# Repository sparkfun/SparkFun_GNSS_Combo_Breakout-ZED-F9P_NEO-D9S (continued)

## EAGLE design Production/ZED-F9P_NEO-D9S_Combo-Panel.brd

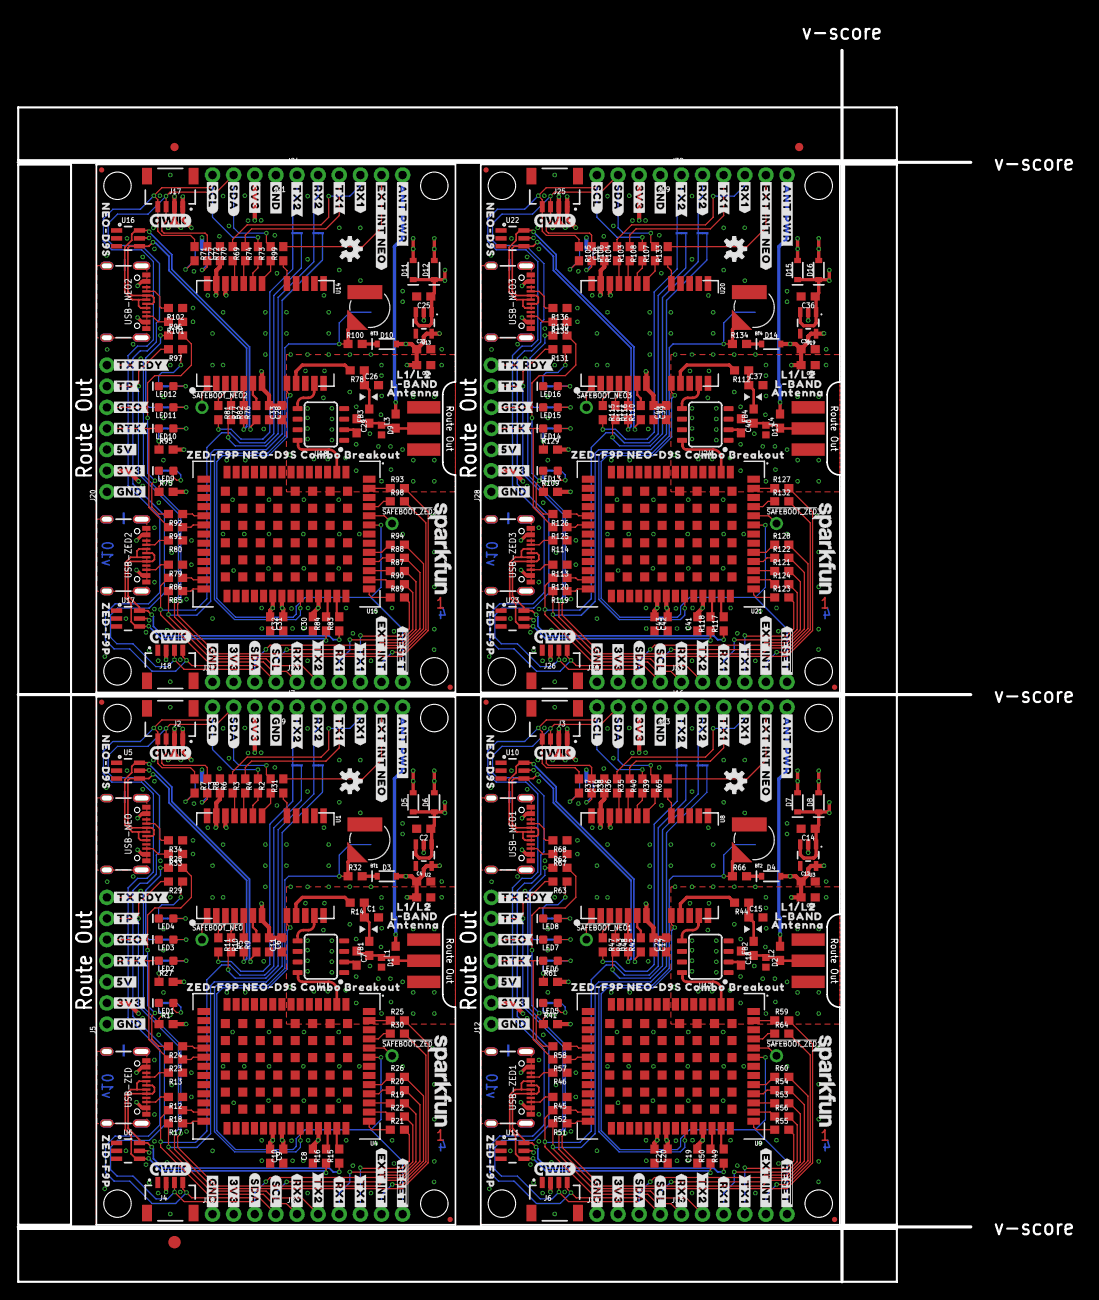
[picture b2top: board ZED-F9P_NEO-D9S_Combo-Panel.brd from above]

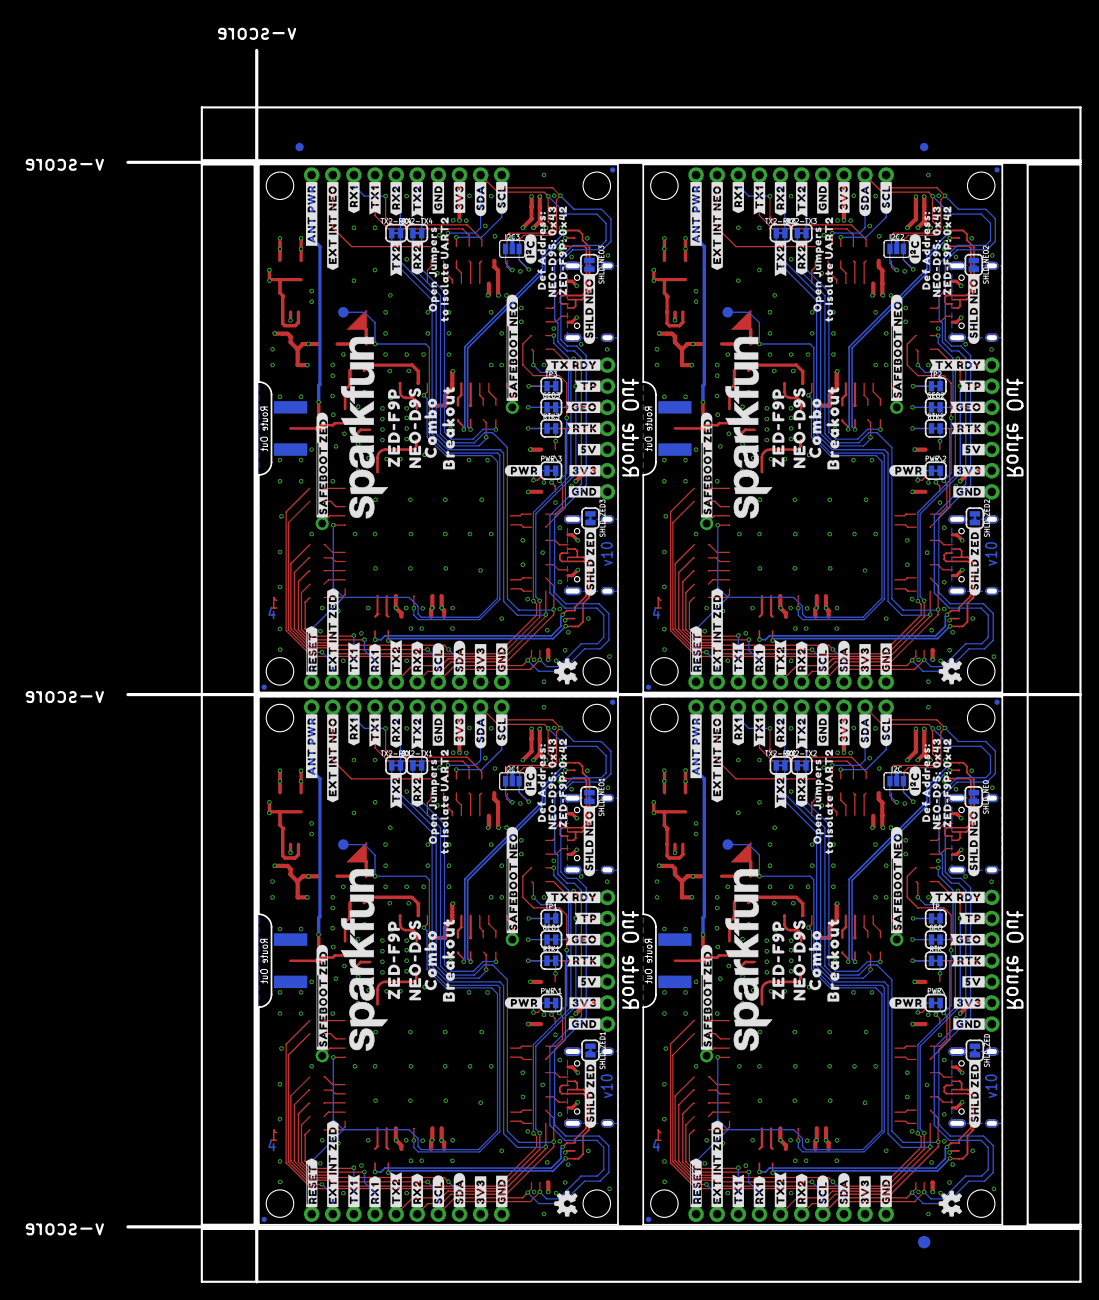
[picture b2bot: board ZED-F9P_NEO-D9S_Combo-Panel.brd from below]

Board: 4 copper layers, 114.6 x 148.1 mm, 714 parts (243 on the bottom side), 300 nets.

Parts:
!SAFEBOOT_NEO!, !SAFEBOOT_NEO!1, !SAFEBOOT_NEO!2, !SAFEBOOT_NEO!3: TEST-POINTPOGO_PTH; 1X01_NO_SILK
!SAFEBOOT_ZED!, !SAFEBOOT_ZED!1, !SAFEBOOT_ZED!2, !SAFEBOOT_ZED!3: TEST-POINTPOGO_PTH; 1X01_NO_SILK
BT1, BT2, BT3, BT4: RELOWABLE_BATTERY_MS421R; MS421R_IV03E
C1, C7, C15, C18, C26, C29, C37, C40: 47pF; 0603
C2, C3, C4, C6, C8, C9, C12, C14, C16, C17, C19, C20, C23, C25, C27, C28, C30, C31, C34, C36, C38, C39, C41, C42: 1.0uF; 0603
C5, C10, C11, C13, C21, C22, C24, C32, C33, C35, C43, C44: 0.1uF; 0603
D1, D2, D9, D13: PESD0402-0402; 0402
D3, D4, D10, D14: 0.5A/40V/420mV; SOD-323
D5, D6, D7, D8, D11, D12, D15, D16: 1A/23V/620mV; SOD-323
E$1, E$2, E$3, E$4: FIDUCIAL-1X2
E$5, E$6: FIDUCIAL-1.5X3
FB1, FB2, FB3, FB4: 30Ω/1.8A; 0603
GEO, GEO1, GEO2, GEO3: JUMPER-SMT_2_NC_TRACE_SILK; SMT-JUMPER_2_NC_TRACE_SILK
I2C, I2C1, I2C2, I2C3: JUMPER-SMT_3_NO_SILK; SMT-JUMPER_3_NO_SILK
J1, J11, J19, J27: ANTENNA-SMA-GROUNDEDEDGE_SMA; SMA-EDGE
J2, J3, J4, J6, J17, J18, J25, J26: Qwiic Right Angle; JST04_1MM_RA
J5, J12, J20, J28: 1X07_NO_SILK
J7, J8, J15, J16, J23, J24, J31, J32: 1X06_NO_SILK
J9, J10, J13, J14, J21, J22, J29, J30: 1X04_NO_SILK
JP1, JP2, JP7, JP8, JP9, JP10, JP15, JP16, JP17, JP18, JP24, JP25, JP31, JP41, JP91, JP101: STAND-OFF
JP3, JP4, JP5, JP6, JP11, JP12, JP13, JP14, JP19, JP20, JP21, JP22, JP23, JP61, JP71, JP81: FIDUCIALUFIDUCIAL; MICRO-FIDUCIAL
L1, L2, L3, L4: DNP; 0603_NO-CREAM
LED1, LED5, LED9, LED13: RED; LED-0603
LED2, LED3, LED4, LED6, LED7, LED8, LED10, LED11, LED12, LED14, LED15, LED16: BLUE; LED-0603
LOGO1, LOGO4, LOGO5, LOGO7, LOGO11, LOGO12, LOGO16, LOGO17: OSHW-LOGOS; OSHW-LOGO-S
LOGO2, LOGO8, LOGO13, LOGO18: SFE_LOGO_NAME.1_INCH; SFE_LOGO_NAME_.1
LOGO3, LOGO6, LOGO9, LOGO10, LOGO14, LOGO15, LOGO19, LOGO20: QWIIC_LOGO_5MM; QWIIC_5MM
PWR\, PWR\1, PWR\2, PWR\3: JUMPER-SMT_2_NC_TRACE_SILK; SMT-JUMPER_2_NC_TRACE_SILK
R1, R41, R75, R109: 4.7k; 0603
R2, R3, R4, R5, R6, R11, R17, R18, R19, R20, R21, R22, R23, R24, R25, R26, R30, R31, R35, R36, R39, R40, R47, R48, R51, R52, R53, R54, R55, R56, R57, R58, R59, R60, R64, R65, R69, R70, R73, R74, R81, R82, R85, R86, R87, R88, R89, R90, R91, R92, R93, R94, R98, R99, R103, R104, R107, R108, R115, R116, R119, R120, R121, R122, R123, R124, R125, R126, R127, R128, R132, R133: 33; 0603
R7, R8, R37, R38, R71, R72, R105, R106: 2.2k; 0603
R9, R10, R15, R16, R42, R43, R49, R50, R76, R77, R83, R84, R110, R111, R117, R118: 27; 0603
R12, R13, R33, R34, R45, R46, R67, R68, R79, R80, R101, R102, R113, R114, R135, R136: 5.1k; 0603
R14, R44, R78, R112: 10; 0603
R27, R28, R29, R61, R62, R63, R95, R96, R97, R129, R130, R131: 1k; 0603
R32, R66, R100, R134: 3.3k; 0603
RTK, RTK1, RTK2, RTK3: JUMPER-SMT_2_NC_TRACE_SILK; SMT-JUMPER_2_NC_TRACE_SILK
RX2-TX1, RX2-TX2, RX2-TX3, RX2-TX4: JUMPER-SMT_2_NC_TRACE_SILK; SMT-JUMPER_2_NC_TRACE_SILK
SHLD_NEO, SHLD_NEO1, SHLD_NEO2, SHLD_NEO3: JUMPER-SMT_2_NC_TRACE_SILK; SMT-JUMPER_2_NC_TRACE_SILK
SHLD_ZED, SHLD_ZED1, SHLD_ZED2, SHLD_ZED3: JUMPER-SMT_2_NC_TRACE_SILK; SMT-JUMPER_2_NC_TRACE_SILK
TP, TP1, TP2, TP3: JUMPER-SMT_2_NC_TRACE_SILK; SMT-JUMPER_2_NC_TRACE_SILK
TX2-RX1, TX2-RX2, TX2-RX3, TX2-RX4: JUMPER-SMT_2_NC_TRACE_SILK; SMT-JUMPER_2_NC_TRACE_SILK
U1, U8, U14, U20: U-BLOX_NEO-D9S-00B; NEO-M9N/M8T/M8U/D9S
U2, U3, U13, U19: 3.3V; SOT23-5
U4, U9, U15, U21: U-BLOX_ZED-F9P; ZED-F9P
U5, U6, U10, U11, U16, U17, U22, U23: ESD Diode; SOT-23-6
U7, U12, U18, U24: BP2G1+_POWER_SPLITTER; XX21
U$1, U$2, U$3, U$38, U$77, U$83, U$161, U$162, U$163, U$241, U$242, U$243: #GND#0
U$4, U$5, U$6, U$84, U$85, U$86, U$164, U$165, U$166, U$244, U$245, U$246: #GND#1
U$7, U$144, U$224, U$304: #SHLD_ZED#15
U$8, U$10, U$126, U$127, U$206, U$207, U$286, U$287: #SDA#0
U$9, U$13, U$130, U$131, U$210, U$211, U$290, U$291: #SCL#0
U$11, U$12, U$128, U$129, U$208, U$209, U$288, U$289: #SDA#1
U$14, U$153, U$233, U$313: L#BAND18
U$15, U$30, U$132, U$133, U$212, U$213, U$292, U$293: #SCL#1
U$16, U$100, U$180, U$260: #RTK#0
U$17, U$101, U$181, U$261: #RTK#1
U$18, U$102, U$182, U$262: #GEO#0
U$19, U$103, U$183, U$263: #GEO#1
U$20, U$87, U$167, U$247: #5V#0
U$21, U$88, U$168, U$248: #5V#6
U$22, U$23, U$56, U$89, U$90, U$97, U$169, U$170, U$177, U$249, U$250, U$257: #3V3#0
U$24, U$25, U$70, U$91, U$92, U$139, U$171, U$172, U$219, U$251, U$252, U$299: #3V3#4
U$26, U$104, U$184, U$264: #TP#0
U$27, U$105, U$185, U$265: #TP#1
U$28, U$106, U$186, U$266: #TX_RDY#0
U$29, U$107, U$187, U$267: #TX_RDY#1
U$31, U$39, U$40, U$112, U$113, U$134, U$192, U$193, U$214, U$272, U$273, U$294: #TX2#0
U$32, U$34, U$35, U$108, U$109, U$135, U$188, U$189, U$215, U$268, U$269, U$295: #RX2#0
U$33, U$151, U$231, U$311: L1#L218
U$36, U$37, U$110, U$111, U$190, U$191, U$270, U$271: #RX2#3
U$41, U$42, U$114, U$115, U$194, U$195, U$274, U$275: #TX2#3
U$43, U$44, U$116, U$117, U$196, U$197, U$276, U$277: #RX1#0
U$45, U$93, U$173, U$253: ##RESET##0
U$46, U$94, U$174, U$254: ##RESET##1
U$47, U$95, U$175, U$255: #EXT_INT#0
U$48, U$140, U$220, U$300: #EXT_INT_ZED#0
U$49, U$50, U$118, U$119, U$198, U$199, U$278, U$279: #RX1#2
U$51, U$57, U$120, U$121, U$200, U$201, U$280, U$281: #TX1#0
U$52, U$96, U$176, U$256: #I�C#0
U$53, U$145, U$225, U$305: #SHLD_NEO#12
U$54, U$152, U$232, U$312: ANTENNA18
U$55, U$147, U$227, U$307: NEO#D9S16
U$58, U$98, U$178, U$258: #ANT_PWR#0
U$59, U$99, U$179, U$259: #ANT_PWR#1
U$60, U$61, U$122, U$123, U$202, U$203, U$282, U$283: #TX1#2
U$62, U$124, U$204, U$284: #EXT_INT_NEO#0
U$63, U$125, U$205, U$285: #EXT_INT_NEO#1
U$64, U$148, U$228, U$308: COMBO16
U$65, U$136, U$216, U$296: ZED#F9P10
U$66, U$137, U$217, U$297: NEO#D9S10
U$67, U$149, U$229, U$309: BREAKOUT17
U$68, U$150, U$230, U$310: SFE_LOGO_NAME_.2
U$69, U$138, U$218, U$298: #PWR#0
U$71, U$142, U$222, U$302: ##SAFEBOOT#_NEO#13
U$72, U$143, U$223, U$303: ##SAFEBOOT#_ZED#14
U$73, U$154, U$234, U$314: OPEN_JUMPERS13
U$74, U$155, U$235, U$315: TO_ISOLATE_UART214
U$75, U$141, U$221, U$301: ZED#F9P_NEO#D9S_COMBO_BREAKOUT0
U$76, U$156, U$236, U$316: DEF_ADDRESS#_12
U$78, U$146, U$226, U$306: ZED#F9P16
U$79, U$157, U$237, U$317: NEO#D9S#13
U$80, U$158, U$238, U$318: ZED#F9P#13
U$81, U$159, U$239, U$319: 0X4313
U$82, U$160, U$240, U$320: 0X4213
USB-NEO, USB-NEO1, USB-NEO2, USB-NEO3: USB Female Type C Connector; USB-C-16P_4LAYER-PADS
USB-ZED, USB-ZED1, USB-ZED2, USB-ZED3: USB Female Type C Connector; USB-C-16P_4LAYER-PADS
V_BKCP, V_BKCP1, V_BKCP2, V_BKCP3: TEST-POINT3X5; PAD.03X.05

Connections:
3.3V: C3.1, C4.1, C5.2, C6.1, C8.2, C9.1, C10.2, C11.2, D3.A, I2C.2, J2.2, J4.2, J5.2, J9.2, J10.2, R1.2, R27.2, U1.7, U1.22, U1.23, U2.5, U4.33, U4.34, U4.38
3.3V1: C12.1, C13.2, C16.1, C17.1, C19.2, C20.1, C21.2, C22.2, D4.A, I2C1.2, J3.2, J6.2, J12.2, J13.2, J14.2, R41.2, R61.2, U3.5, U8.7, U8.22, U8.23, U9.33, U9.34, U9.38
3.3V2: C23.1, C24.2, C27.1, C28.1, C30.2, C31.1, C32.2, C33.2, D10.A, I2C2.2, J17.2, J18.2, J20.2, J21.2, J22.2, R75.2, R95.2, U13.5, U14.7, U14.22, U14.23, U15.33, U15.34, U15.38
3.3V3: C34.1, C35.2, C38.1, C39.1, C41.2, C42.1, C43.2, C44.2, D14.A, I2C3.2, J25.2, J26.2, J28.2, J29.2, J30.2, R109.2, R129.2, U19.5, U20.7, U20.22, U20.23, U21.33, U21.34, U21.38
5V: C2.1, D5.C, D6.C, J5.3, U2.1, U2.3
5V1: C14.1, D7.C, D8.C, J12.3, U3.1, U3.3
5V2: C25.1, D11.C, D12.C, J20.3, U13.1, U13.3
5V3: C36.1, D15.C, D16.C, J28.3, U19.1, U19.3
!RESET!: J8.6, U1.8, U4.49
!RESET!1: J15.6, U8.8, U9.49
!RESET!2: J23.6, U14.8, U15.49
!RESET!3: J31.6, U20.8, U21.49
!SAFEBOOT_NEO!: !SAFEBOOT_NEO!.1, U1.1
!SAFEBOOT_NEO!1: !SAFEBOOT_NEO!1.1, U8.1
!SAFEBOOT_NEO!2: !SAFEBOOT_NEO!2.1, U14.1
!SAFEBOOT_NEO!3: !SAFEBOOT_NEO!3.1, U20.1
!SAFEBOOT_ZED!: !SAFEBOOT_ZED!.1, U4.50
!SAFEBOOT_ZED!1: !SAFEBOOT_ZED!1.1, U9.50
!SAFEBOOT_ZED!2: !SAFEBOOT_ZED!2.1, U15.50
!SAFEBOOT_ZED!3: !SAFEBOOT_ZED!3.1, U21.50
ANT: C7.2, U7.2
ANT1: C18.2, U12.2
ANT2: C29.2, U18.2
ANT3: C40.2, U24.2
ANT_NEO: U1.11, U7.5
ANT_NEO1: U8.11, U12.5
ANT_NEO2: U14.11, U18.5
ANT_NEO3: U20.11, U24.5
ANT_PWR: J7.6, L1.2
ANT_PWR1: J16.6, L2.2
ANT_PWR2: J24.6, L3.2
ANT_PWR3: J32.6, L4.2
ANT_VCC: C1.1, FB1.2, R14.1
ANT_VCC1: C15.1, FB2.2, R44.1
ANT_VCC2: C26.1, FB3.2, R78.1
ANT_VCC3: C37.1, FB4.2, R112.1
ANT_ZED: U4.2, U7.8
ANT_ZED1: U9.2, U12.8
ANT_ZED2: U15.2, U18.8
ANT_ZED3: U21.2, U24.8
D+_NEO: R9.1, U5.6, USB-NEO.A6, USB-NEO.B6
D+_NEO1: R42.1, U10.6, USB-NEO1.A6, USB-NEO1.B6
D+_NEO2: R76.1, U16.6, USB-NEO2.A6, USB-NEO2.B6
D+_NEO3: R110.1, U22.6, USB-NEO3.A6, USB-NEO3.B6
D+_ZED: R15.1, U6.6, USB-ZED.A6, USB-ZED.B6
D+_ZED1: R49.1, U11.6, USB-ZED1.A6, USB-ZED1.B6
D+_ZED2: R83.1, U17.6, USB-ZED2.A6, USB-ZED2.B6
D+_ZED3: R117.1, U23.6, USB-ZED3.A6, USB-ZED3.B6
D-_NEO: R10.1, U5.4, USB-NEO.A7, USB-NEO.B7
D-_NEO1: R43.1, U10.4, USB-NEO1.A7, USB-NEO1.B7
D-_NEO2: R77.1, U16.4, USB-NEO2.A7, USB-NEO2.B7
D-_NEO3: R111.1, U22.4, USB-NEO3.A7, USB-NEO3.B7
D-_ZED: R16.1, U6.4, USB-ZED.A7, USB-ZED.B7
D-_ZED1: R50.1, U11.4, USB-ZED1.A7, USB-ZED1.B7
D-_ZED2: R84.1, U17.4, USB-ZED2.A7, USB-ZED2.B7
D-_ZED3: R118.1, U23.4, USB-ZED3.A7, USB-ZED3.B7
EXT_INT_NEO: J7.5, R31.2
EXT_INT_NEO1: J16.5, R65.2
EXT_INT_NEO2: J24.5, R99.2
EXT_INT_NEO3: J32.5, R133.2
EXT_INT_ZED: J8.5, R30.2
EXT_INT_ZED1: J15.5, R64.2
EXT_INT_ZED2: J23.5, R98.2
EXT_INT_ZED3: J31.5, R132.2
GEO: J5.5, R24.2, R28.2
GEO1: J12.5, R58.2, R62.2
GEO2: J20.5, R92.2, R96.2
GEO3: J28.5, R126.2, R130.2
GND: BT1.-, C1.2, C2.2, C3.2, C4.2, C5.1, C6.2, C8.1, C9.2, C10.1, C11.1, D1.2, J1.GND@0, J1.GND@1, J1.GND@2, J1.GND@3, J2.1, J4.1, J5.1, J9.1, J10.1, LED1.C, LED3.C, LED4.C, R12.1, R13.1, R33.1, R34.1, SHLD_NEO.1, SHLD_ZED.1, U1.10, U1.12, U1.13, U1.24, U2.2, U4.1, U4.3, U4.12, U4.14, U4.32, U4.37, U4.41, U4.48, U4.55, U4.56, U4.57, U4.58, U4.59, U4.60, U4.61, U4.62, U4.63, U4.64, U4.65, U4.66, U4.67, U4.68, U4.69, U4.70, U4.71, U4.72, U4.73, U4.74, U4.75, U4.76, U4.77, U4.78, U4.79, U4.80, U4.81, U4.82, U4.83, U4.84, U4.85, U4.86, U4.87, U4.88, U4.89, U4.90, U4.91, U4.92, U4.93, U4.94, U4.95, U4.96, U4.97, U4.98, U4.99, U4.100, U4.101, U4.102, U5.2, U6.2, U7.1, U7.3, U7.4, U7.6, U7.7, USB-NEO.GND, USB-NEO.GND2, USB-ZED.GND, USB-ZED.GND2
GND1: BT2.-, C12.2, C13.1, C14.2, C15.2, C16.2, C17.2, C19.1, C20.2, C21.1, C22.1, D2.2, J3.1, J6.1, J11.GND@0, J11.GND@1, J11.GND@2, J11.GND@3, J12.1, J13.1, J14.1, LED5.C, LED7.C, LED8.C, R45.1, R46.1, R67.1, R68.1, SHLD_NEO1.1, SHLD_ZED1.1, U3.2, U8.10, U8.12, U8.13, U8.24, U9.1, U9.3, U9.12, U9.14, U9.32, U9.37, U9.41, U9.48, U9.55, U9.56, U9.57, U9.58, U9.59, U9.60, U9.61, U9.62, U9.63, U9.64, U9.65, U9.66, U9.67, U9.68, U9.69, U9.70, U9.71, U9.72, U9.73, U9.74, U9.75, U9.76, U9.77, U9.78, U9.79, U9.80, U9.81, U9.82, U9.83, U9.84, U9.85, U9.86, U9.87, U9.88, U9.89, U9.90, U9.91, U9.92, U9.93, U9.94, U9.95, U9.96, U9.97, U9.98, U9.99, U9.100, U9.101, U9.102, U10.2, U11.2, U12.1, U12.3, U12.4, U12.6, U12.7, USB-NEO1.GND, USB-NEO1.GND2, USB-ZED1.GND, USB-ZED1.GND2
GND2: BT3.-, C23.2, C24.1, C25.2, C26.2, C27.2, C28.2, C30.1, C31.2, C32.1, C33.1, D9.2, J17.1, J18.1, J19.GND@0, J19.GND@1, J19.GND@2, J19.GND@3, J20.1, J21.1, J22.1, LED9.C, LED11.C, LED12.C, R79.1, R80.1, R101.1, R102.1, SHLD_NEO2.1, SHLD_ZED2.1, U13.2, U14.10, U14.12, U14.13, U14.24, U15.1, U15.3, U15.12, U15.14, U15.32, U15.37, U15.41, U15.48, U15.55, U15.56, U15.57, U15.58, U15.59, U15.60, U15.61, U15.62, U15.63, U15.64, U15.65, U15.66, U15.67, U15.68, U15.69, U15.70, U15.71, U15.72, U15.73, U15.74, U15.75, U15.76, U15.77, U15.78, U15.79, U15.80, U15.81, U15.82, U15.83, U15.84, U15.85, U15.86, U15.87, U15.88, U15.89, U15.90, U15.91, U15.92, U15.93, U15.94, U15.95, U15.96, U15.97, U15.98, U15.99, U15.100, U15.101, U15.102, U16.2, U17.2, U18.1, U18.3, U18.4, U18.6, U18.7, USB-NEO2.GND, USB-NEO2.GND2, USB-ZED2.GND, USB-ZED2.GND2
GND3: BT4.-, C34.2, C35.1, C36.2, C37.2, C38.2, C39.2, C41.1, C42.2, C43.1, C44.1, D13.2, J25.1, J26.1, J27.GND@0, J27.GND@1, J27.GND@2, J27.GND@3, J28.1, J29.1, J30.1, LED13.C, LED15.C, LED16.C, R113.1, R114.1, R135.1, R136.1, SHLD_NEO3.1, SHLD_ZED3.1, U19.2, U20.10, U20.12, U20.13, U20.24, U21.1, U21.3, U21.12, U21.14, U21.32, U21.37, U21.41, U21.48, U21.55, U21.56, U21.57, U21.58, U21.59, U21.60, U21.61, U21.62, U21.63, U21.64, U21.65, U21.66, U21.67, U21.68, U21.69, U21.70, U21.71, U21.72, U21.73, U21.74, U21.75, U21.76, U21.77, U21.78, U21.79, U21.80, U21.81, U21.82, U21.83, U21.84, U21.85, U21.86, U21.87, U21.88, U21.89, U21.90, U21.91, U21.92, U21.93, U21.94, U21.95, U21.96, U21.97, U21.98, U21.99, U21.100, U21.101, U21.102, U22.2, U23.2, U24.1, U24.3, U24.4, U24.6, U24.7, USB-NEO3.GND, USB-NEO3.GND2, USB-ZED3.GND, USB-ZED3.GND2
unnamed: PWR\.2, R1.1
unnamed: R3.1, U1.20
unnamed: R2.1, U1.18
unnamed: R4.1, U1.19
unnamed: I2C.1, R8.2
unnamed: R6.1, U1.21
unnamed: R12.2, USB-ZED.B5
unnamed: I2C.3, R7.2
unnamed: R13.2, USB-ZED.A5
unnamed: LED1.A, PWR\.1
unnamed: R9.2, U1.6
unnamed: R10.2, U1.5
unnamed: D3.C, R32.2
unnamed: R11.1, U1.3
unnamed: R5.1, U1.4
unnamed: R15.2, U4.40
unnamed: R16.2, U4.39
unnamed: R19.1, U4.44
unnamed: R20.1, U4.45
unnamed: R21.1, U4.42
unnamed: R22.1, U4.43
unnamed: R26.1, U4.46
unnamed: LED2.A, RTK.1
unnamed: R17.1, U4.27
unnamed: R18.1, U4.26
unnamed: GEO.1, LED3.A
unnamed: LED4.A, TP.1
unnamed: R27.1, RTK.2
unnamed: GEO.2, R28.1
unnamed: R29.1, TP.2
unnamed: R30.1, U4.51
unnamed: R31.1, U1.17
unnamed: R33.2, USB-NEO.B5
unnamed: R34.2, USB-NEO.A5
unnamed: R23.1, U4.20
unnamed: R24.1, U4.19
unnamed: R25.1, U4.53
unnamed: I2C1.1, R38.2
unnamed: I2C1.3, R37.2
unnamed: R42.2, U8.6
unnamed: R43.2, U8.5
unnamed: R45.2, USB-ZED1.B5
unnamed: R46.2, USB-ZED1.A5
unnamed: R47.1, U8.3
unnamed: R48.1, U8.4
unnamed: R35.1, U8.20
unnamed: R36.1, U8.21
unnamed: R39.1, U8.18
unnamed: R40.1, U8.19
unnamed: R49.2, U9.40
unnamed: R50.2, U9.39
unnamed: R53.1, U9.44
unnamed: R54.1, U9.45
unnamed: R55.1, U9.42
unnamed: R56.1, U9.43
unnamed: R51.1, U9.27
unnamed: R52.1, U9.26
unnamed: R60.1, U9.46
unnamed: LED6.A, RTK1.1
unnamed: GEO1.1, LED7.A
unnamed: LED8.A, TP1.1
unnamed: R61.1, RTK1.2
unnamed: GEO1.2, R62.1
unnamed: R63.1, TP1.2
unnamed: R57.1, U9.20
unnamed: R58.1, U9.19
unnamed: R59.1, U9.53
unnamed: R64.1, U9.51
unnamed: R65.1, U8.17
unnamed: D4.C, R66.2
unnamed: R67.2, USB-NEO1.B5
unnamed: R68.2, USB-NEO1.A5
unnamed: PWR\1.2, R41.1
unnamed: LED5.A, PWR\1.1
unnamed: I2C2.1, R72.2
unnamed: I2C2.3, R71.2
unnamed: R76.2, U14.6
unnamed: R77.2, U14.5
unnamed: R79.2, USB-ZED2.B5
unnamed: R80.2, USB-ZED2.A5
unnamed: R81.1, U14.3
unnamed: R82.1, U14.4
unnamed: R69.1, U14.20
unnamed: R70.1, U14.21
unnamed: R73.1, U14.18
unnamed: R74.1, U14.19
unnamed: R83.2, U15.40
unnamed: R84.2, U15.39
unnamed: R87.1, U15.44
unnamed: R88.1, U15.45
unnamed: R89.1, U15.42
unnamed: R90.1, U15.43
unnamed: R85.1, U15.27
unnamed: R86.1, U15.26
unnamed: R94.1, U15.46
unnamed: LED10.A, RTK2.1
unnamed: GEO2.1, LED11.A
unnamed: LED12.A, TP2.1
unnamed: R95.1, RTK2.2
unnamed: GEO2.2, R96.1
unnamed: R97.1, TP2.2
unnamed: R91.1, U15.20
unnamed: R92.1, U15.19
unnamed: R93.1, U15.53
unnamed: R98.1, U15.51
unnamed: R99.1, U14.17
unnamed: D10.C, R100.2
unnamed: R101.2, USB-NEO2.B5
unnamed: R102.2, USB-NEO2.A5
unnamed: PWR\2.2, R75.1
unnamed: LED9.A, PWR\2.1
unnamed: I2C3.1, R106.2
unnamed: I2C3.3, R105.2
unnamed: R110.2, U20.6
unnamed: R111.2, U20.5
unnamed: R113.2, USB-ZED3.B5
unnamed: R114.2, USB-ZED3.A5
unnamed: R115.1, U20.3
unnamed: R116.1, U20.4
unnamed: R103.1, U20.20
unnamed: R104.1, U20.21
unnamed: R107.1, U20.18
unnamed: R108.1, U20.19
unnamed: R117.2, U21.40
unnamed: R118.2, U21.39
unnamed: R121.1, U21.44
unnamed: R122.1, U21.45
unnamed: R123.1, U21.42
unnamed: R124.1, U21.43
unnamed: R119.1, U21.27
unnamed: R120.1, U21.26
unnamed: R128.1, U21.46
unnamed: LED14.A, RTK3.1
unnamed: GEO3.1, LED15.A
unnamed: LED16.A, TP3.1
unnamed: R129.1, RTK3.2
unnamed: GEO3.2, R130.1
unnamed: R131.1, TP3.2
unnamed: R125.1, U21.20
unnamed: R126.1, U21.19
unnamed: R127.1, U21.53
unnamed: R132.1, U21.51
unnamed: R133.1, U20.17
unnamed: D14.C, R134.2
unnamed: R135.2, USB-NEO3.B5
unnamed: R136.2, USB-NEO3.A5
unnamed: PWR\3.2, R109.1
unnamed: LED13.A, PWR\3.1
RTK: J5.4, LED2.C, R23.2
RTK1: J12.4, LED6.C, R57.2
RTK2: J20.4, LED10.C, R91.2
RTK3: J28.4, LED14.C, R125.2
RXD1_NEO: J7.4, R6.2
RXD1_NEO1: J16.4, R36.2
RXD1_NEO2: J24.4, R70.2
RXD1_NEO3: J32.4, R104.2
RXD1_ZED: J8.3, R22.2
RXD1_ZED1: J15.3, R56.2
RXD1_ZED2: J23.3, R90.2
RXD1_ZED3: J31.3, R124.2
RXD2_NEO: J7.2, R5.2, TX2-RX2.2
RXD2_NEO1: J16.2, R48.2, TX2-RX1.2
RXD2_NEO2: J24.2, R82.2, TX2-RX3.2
RXD2_NEO3: J32.2, R116.2, TX2-RX4.2
RXD2_ZED: J8.1, R18.2, RX2-TX2.1
RXD2_ZED1: J15.1, R52.2, RX2-TX1.1
RXD2_ZED2: J23.1, R86.2, RX2-TX3.1
RXD2_ZED3: J31.1, R120.2, RX2-TX4.1
SCL: J2.4, J4.4, J9.4, J10.4, R4.2, R7.1, R20.2
SCL1: J3.4, J6.4, J13.4, J14.4, R37.1, R40.2, R54.2
SCL2: J17.4, J18.4, J21.4, J22.4, R71.1, R74.2, R88.2
SCL3: J25.4, J26.4, J29.4, J30.4, R105.1, R108.2, R122.2
SDA: J2.3, J4.3, J9.3, J10.3, R2.2, R8.1, R19.2
SDA1: J3.3, J6.3, J13.3, J14.3, R38.1, R39.2, R53.2
SDA2: J17.3, J18.3, J21.3, J22.3, R72.1, R73.2, R87.2
SDA3: J25.3, J26.3, J29.3, J30.3, R106.1, R107.2, R121.2
SHIELD_NEO: SHLD_NEO.2, USB-NEO.SHLD1, USB-NEO.SHLD2, USB-NEO.SHLD3, USB-NEO.SHLD4
SHIELD_NEO1: SHLD_NEO1.2, USB-NEO1.SHLD1, USB-NEO1.SHLD2, USB-NEO1.SHLD3, USB-NEO1.SHLD4
SHIELD_NEO2: SHLD_NEO2.2, USB-NEO2.SHLD1, USB-NEO2.SHLD2, USB-NEO2.SHLD3, USB-NEO2.SHLD4
SHIELD_NEO3: SHLD_NEO3.2, USB-NEO3.SHLD1, USB-NEO3.SHLD2, USB-NEO3.SHLD3, USB-NEO3.SHLD4
SHIELD_ZED: SHLD_ZED.2, USB-ZED.SHLD1, USB-ZED.SHLD2, USB-ZED.SHLD3, USB-ZED.SHLD4
SHIELD_ZED1: SHLD_ZED1.2, USB-ZED1.SHLD1, USB-ZED1.SHLD2, USB-ZED1.SHLD3, USB-ZED1.SHLD4
SHIELD_ZED2: SHLD_ZED2.2, USB-ZED2.SHLD1, USB-ZED2.SHLD2, USB-ZED2.SHLD3, USB-ZED2.SHLD4
SHIELD_ZED3: SHLD_ZED3.2, USB-ZED3.SHLD1, USB-ZED3.SHLD2, USB-ZED3.SHLD3, USB-ZED3.SHLD4
SMA: C7.1, D1.1, FB1.1, J1.SIG, L1.1
SMA1: C18.1, D2.1, FB2.1, J11.SIG, L2.1
SMA2: C29.1, D9.1, FB3.1, J19.SIG, L3.1
SMA3: C40.1, D13.1, FB4.1, J27.SIG, L4.1
TP: J5.6, R25.2, R29.2
TP1: J12.6, R59.2, R63.2
TP2: J20.6, R93.2, R97.2
TP3: J28.6, R127.2, R131.2
TXD1_NEO: J7.3, R3.2
TXD1_NEO1: J16.3, R35.2
TXD1_NEO2: J24.3, R69.2
TXD1_NEO3: J32.3, R103.2
TXD1_ZED: J8.4, R21.2
TXD1_ZED1: J15.4, R55.2
TXD1_ZED2: J23.4, R89.2
TXD1_ZED3: J31.4, R123.2
TXD2_NEO: J7.1, R11.2, RX2-TX2.2
TXD2_NEO1: J16.1, R47.2, RX2-TX1.2
TXD2_NEO2: J24.1, R81.2, RX2-TX3.2
TXD2_NEO3: J32.1, R115.2, RX2-TX4.2
TXD2_ZED: J8.2, R17.2, TX2-RX2.1
TXD2_ZED1: J15.2, R51.2, TX2-RX1.1
TXD2_ZED2: J23.2, R85.2, TX2-RX3.1
TXD2_ZED3: J31.2, R119.2, TX2-RX4.1
TX_RDY: J5.7, R26.2
TX_RDY1: J12.7, R60.2
TX_RDY2: J20.7, R94.2
TX_RDY3: J28.7, R128.2
VCC_RF: R14.2, U1.9
VCC_RF1: R44.2, U8.9
VCC_RF2: R78.2, U14.9
VCC_RF3: R112.2, U20.9
V_BKCP: BT1.+, R32.1, U4.36, V_BKCP.1
V_BKCP1: BT2.+, R66.1, U9.36, V_BKCP1.1
V_BKCP2: BT3.+, R100.1, U15.36, V_BKCP2.1
V_BKCP3: BT4.+, R134.1, U21.36, V_BKCP3.1
V_USB: D5.A, U6.5, USB-ZED.VBUS1, USB-ZED.VBUS2
V_USB1: D7.A, U11.5, USB-ZED1.VBUS1, USB-ZED1.VBUS2
V_USB2: D11.A, U17.5, USB-ZED2.VBUS1, USB-ZED2.VBUS2
V_USB3: D15.A, U23.5, USB-ZED3.VBUS1, USB-ZED3.VBUS2
V_USB_1: D8.A, U10.5, USB-NEO1.VBUS1, USB-NEO1.VBUS2
V_USB_2: D6.A, U5.5, USB-NEO.VBUS1, USB-NEO.VBUS2
V_USB_3: D12.A, U16.5, USB-NEO2.VBUS1, USB-NEO2.VBUS2
V_USB_4: D16.A, U22.5, USB-NEO3.VBUS1, USB-NEO3.VBUS2

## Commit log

2023-05-22 Initial transfer from SparkX repository
2023-05-24 Updates various text and symbols
    * Replaces ESD Diodes and Antenna Splitter Diode with larger packages
2023-05-25 Changes 90 Ohm impedance calculation to decrease trace width
    * Adds additional measures
    * Updates silk
    * Adds polygons to USB shield
    * Adds four layer numbers
    * Updated ordering instructions
    * Routes new antenna splitter
2023-05-26 Fixes ESD diode
    * Adds L-Band text/silk to relevant Antenna notes
2023-05-26 Re-adds UART text on UART Jumpers
    * Updates the default address text so it's not so wordy.
2023-05-26 Normalizes the drill sizes
2023-05-26 Adds a few vias, fixes some ground pour
2023-05-30 Updates note for USB 90 Ohm impedance calculation
    * Moves all silk out towards the PTH's
2023-05-30 Updates BP2G1+ with minor corrections
2023-05-30 Replaces 1x6 PTH connector with no SKU
2023-05-30 Adds new panel
2023-06-01 Adds new panel - bottom silk change
2023-06-01 Renames panel zip file to include version
2023-07-19 Initial checkin of docs
    Initial checkin of GitHub docs framework
2023-07-20 Update README.md
    Fixing image
2023-07-20 Test Update
    Test Update
2023-07-21 Update to page names
2023-07-21 Revert "Update to page names"
    This reverts commit 72c774f63e1be3518ddcd52e1e8004fc530dbb57.
2023-07-21 Retest page names
2023-07-21 Changing software pages
2023-07-21 Updating software pages (again)
2023-07-21 Page swap one more time
2023-07-21 Clean up and link fixing
2023-07-24 Updating hard copy code
2023-07-25 Adding final pic for hardware hookup
2023-07-26 Adding GPS forums to links
2024-03-04 Deployed 94e78bc with MkDocs version: 1.5.3
2025-02-20 Update index.md
    Updating missing image
2025-02-21 Update L-Band coverage
2025-02-21 Remove EU L-Band frequency
2025-02-21 Deployed 0c63e71 with MkDocs version: 1.6.1
2025-05-16 Emphasize B2B Customers Only
2025-05-16 Figure reformatting
2025-05-16 Remove fontawesome-solid-cart
2025-05-16 Rename mkdocs.yml in workflows
2025-05-16 Deployed 9e1de07 with MkDocs version: 1.6.1
2025-05-16 Deployed 74b8012 with MkDocs version: 1.6.1
2025-05-16 Deployed 7fd56a0 with MkDocs version: 1.6.1
2025-05-16 Deployed 5cfc48f with MkDocs version: 1.6.1
2025-05-16 Deployed 9057640 with MkDocs version: 1.6.1
2025-05-16 Update Docs
    Update build workflow
    Update mkdocs configuration
    Update documentation
2025-05-16 Deployed b98af87 with MkDocs version: 1.6.1
2025-05-19 Deployed a8fba6f with MkDocs version: 1.6.1
2025-05-19 Deployed a3cac16 with MkDocs version: 1.6.1
2025-05-19 Deployed 11add6a with MkDocs version: 1.6.1
2025-05-19 Deployed 28ea82b with MkDocs version: 1.6.1
2025-05-19 Deployed cf1d37a with MkDocs version: 1.6.1
2025-05-19 Deployed 6682812 with MkDocs version: 1.6.1
2026-06-03 Deployed 8d96103 with MkDocs version: 1.6.1
